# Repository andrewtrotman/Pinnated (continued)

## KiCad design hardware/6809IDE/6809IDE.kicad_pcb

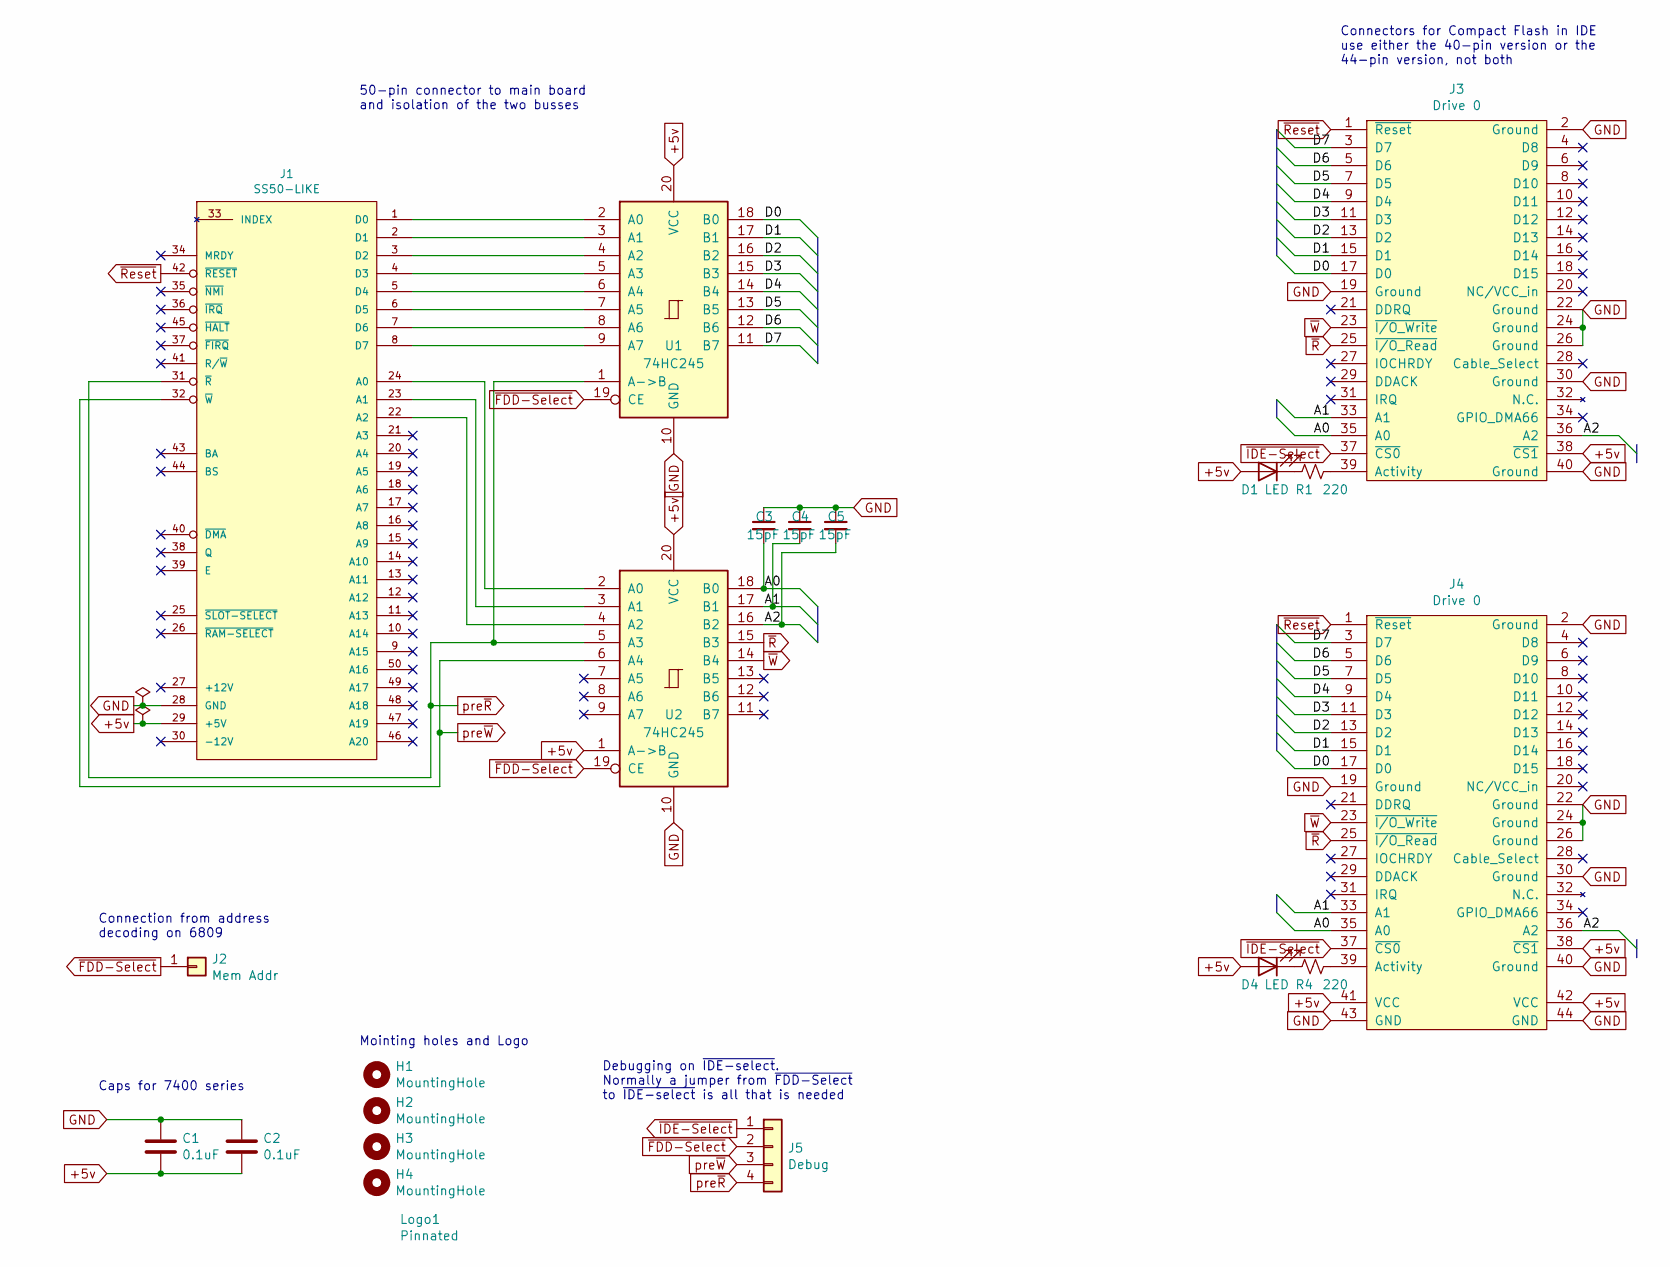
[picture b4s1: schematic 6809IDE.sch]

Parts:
C1, C2: 0.1uF; C_Disc_D5.0mm_W2.5mm_P5.00mm
C3, C4, C5: 15pF; C_Disc_D5.0mm_W2.5mm_P2.50mm
D1, D4: LED; LED_D5.0mm
H1, H2, H3, H4: MountingHole; MountingHole_3.2mm_M3_ISO14580_Pad
J1: SS50-LIKE; PinHeader_2x25_P2.54mm_Vertical
J2: Mem Addr; PinHeader_1x01_P2.54mm_Vertical
J3: Drive 0; PinHeader_2x20_P2.54mm_Vertical
J4: Drive 0; PinHeader_2x22_P2.00mm_Vertical
J5: Debug; PinHeader_1x04_P2.54mm_Vertical
Logo1: Pinnated; Pinnule
R1, R4: 220; R_Axial_DIN0309_L9.0mm_D3.2mm_P12.70mm_Horizontal
U1, U2: 74HC245; DIP-20_W7.62mm_LongPads

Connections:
+5v: C1.2, C2.2, D1.2 (A), D4.2 (A), J1.29 (+5V), J3.38 (~CS1), J4.38 (~CS1), J4.41 (VCC), J4.42 (VCC), U1.20 (VCC), U2.1 (A->B), U2.20 (VCC)
/A0: C3.2, J3.35 (A0), J4.35 (A0), U2.18 (B0)
/A1: C4.2, J3.33 (A1), J4.33 (A1), U2.17 (B1)
/A2: C5.2, J3.36 (A2), J4.36 (A2), U2.16 (B2)
/D0: J3.17 (D0), J4.17 (D0), U1.18 (B0)
/D1: J3.15 (D1), J4.15 (D1), U1.17 (B1)
/D2: J3.13 (D2), J4.13 (D2), U1.16 (B2)
/D3: J3.11 (D3), J4.11 (D3), U1.15 (B3)
/D4: J3.9 (D4), J4.9 (D4), U1.14 (B4)
/D5: J3.7 (D5), J4.7 (D5), U1.13 (B5)
/D6: J3.5 (D6), J4.5 (D6), U1.12 (B6)
/D7: J3.3 (D7), J4.3 (D7), U1.11 (B7)
GND: C1.1, C2.1, C3.1, C4.1, C5.1, J1.28 (GND), J3.2 (Ground), J3.19 (Ground), J3.22 (Ground), J3.24 (Ground), J3.26 (Ground), J3.30 (Ground), J3.40 (Ground), J4.2 (Ground), J4.19 (Ground), J4.22 (Ground), J4.24 (Ground), J4.26 (Ground), J4.30 (Ground), J4.40 (Ground), J4.43 (GND), J4.44 (GND), U1.10 (GND), U2.10 (GND)
unnamed: D1.1 (K), R1.2
unnamed: D4.1 (K), R4.2
unnamed: J1.1 (D0), U1.2 (A0)
unnamed: J1.2 (D1), U1.3 (A1)
unnamed: J1.3 (D2), U1.4 (A2)
unnamed: J1.4 (D3), U1.5 (A3)
unnamed: J1.5 (D4), U1.6 (A4)
unnamed: J1.6 (D5), U1.7 (A5)
unnamed: J1.7 (D6), U1.8 (A6)
unnamed: J1.8 (D7), U1.9 (A7)
unnamed: J1.22 (A2), U2.4 (A2)
unnamed: J1.23 (A1), U2.3 (A1)
unnamed: J1.24 (A0), U2.2 (A0)
unnamed: J3.39 (Activity), R1.1
unnamed: J4.39 (Activity), R4.1
pre~R: J1.31 (~R), J5.4, U1.1 (A->B), U2.5 (A3)
pre~W: J1.32 (~W), J5.3, U2.6 (A4)
~FDD-Select: J2.1, J5.2, U1.19 (CE), U2.19 (CE)
~IDE-Select: J3.37 (~CS0), J4.37 (~CS0), J5.1
~R: J3.25 (~I/O_Read), J4.25 (~I/O_Read), U2.15 (B3)
~Reset: J1.42 (~RESET), J3.1 (~Reset), J4.1 (~Reset)
~W: J3.23 (~I/O_Write), J4.23 (~I/O_Write), U2.14 (B4)

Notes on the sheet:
Debugging on ~IDE-select~. Normally a jumper from ~FDD-Select~ to ~IDE-select~ is all that is needed
Mointing holes and Logo
Caps for 7400 series
Connectors for Compact Flash in IDE use either the 40-pin version or the 44-pin version, not both
Connection from address decoding on 6809
50-pin connector to main board and isolation of the two busses

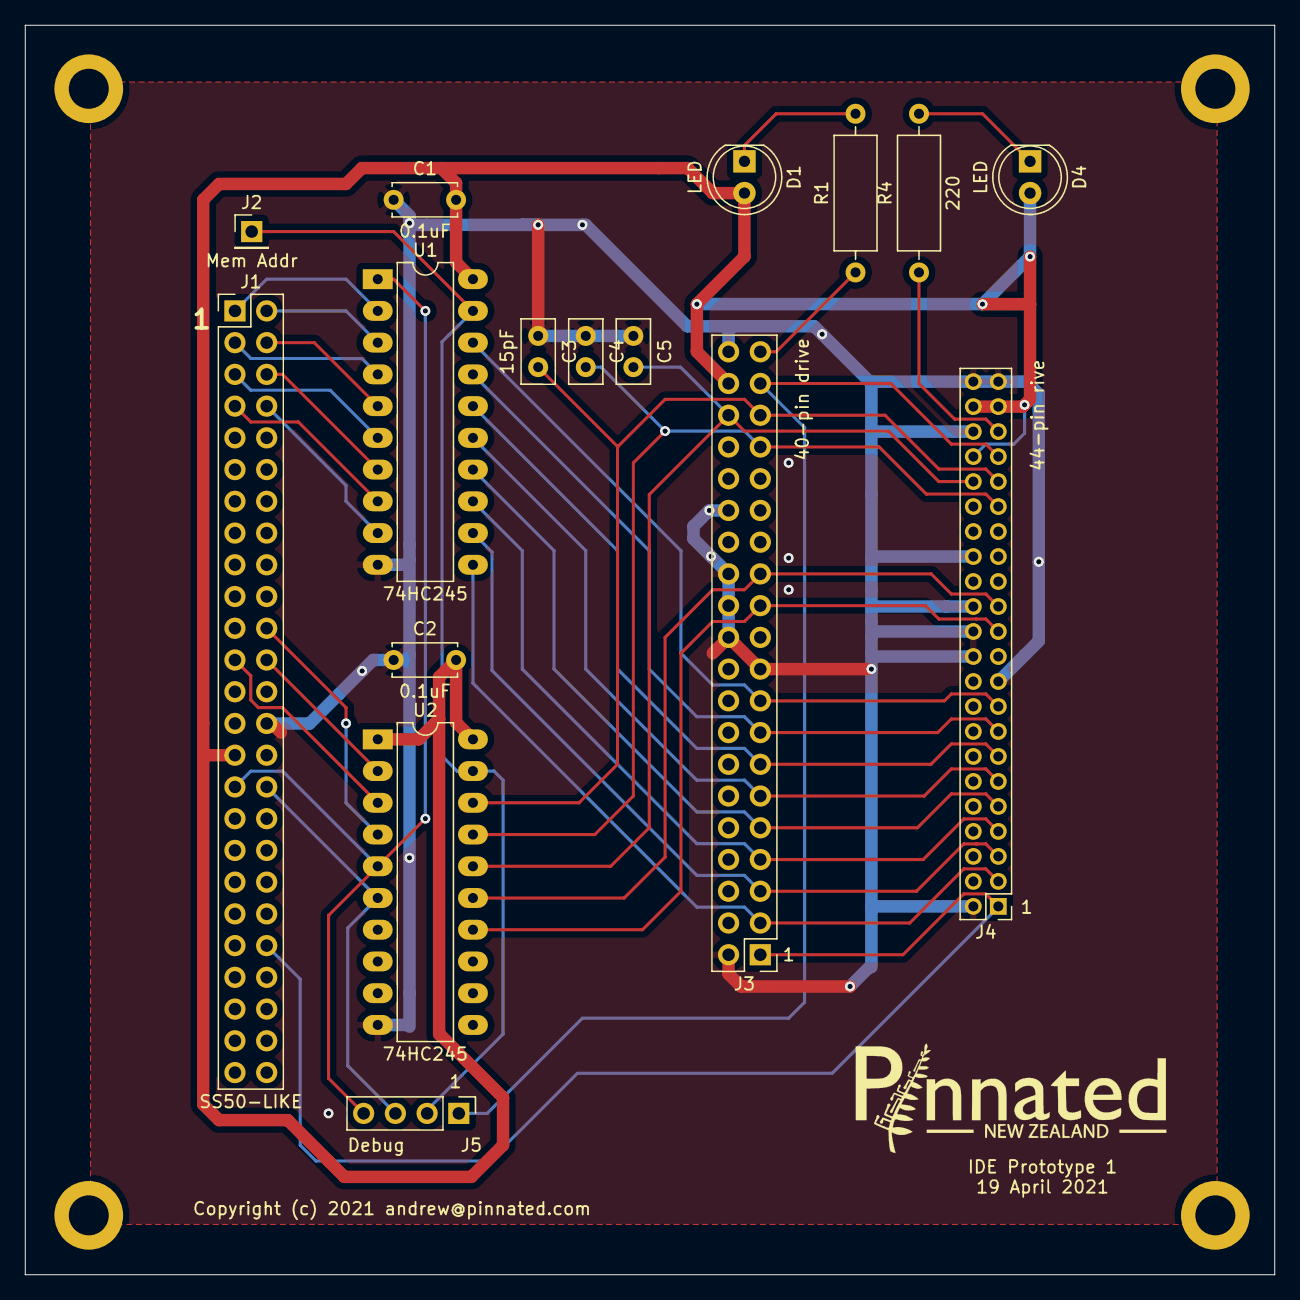
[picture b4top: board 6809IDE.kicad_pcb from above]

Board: 2 copper layers, 100.0 x 100.0 mm, 20 parts (0 on the bottom side), 35 nets.

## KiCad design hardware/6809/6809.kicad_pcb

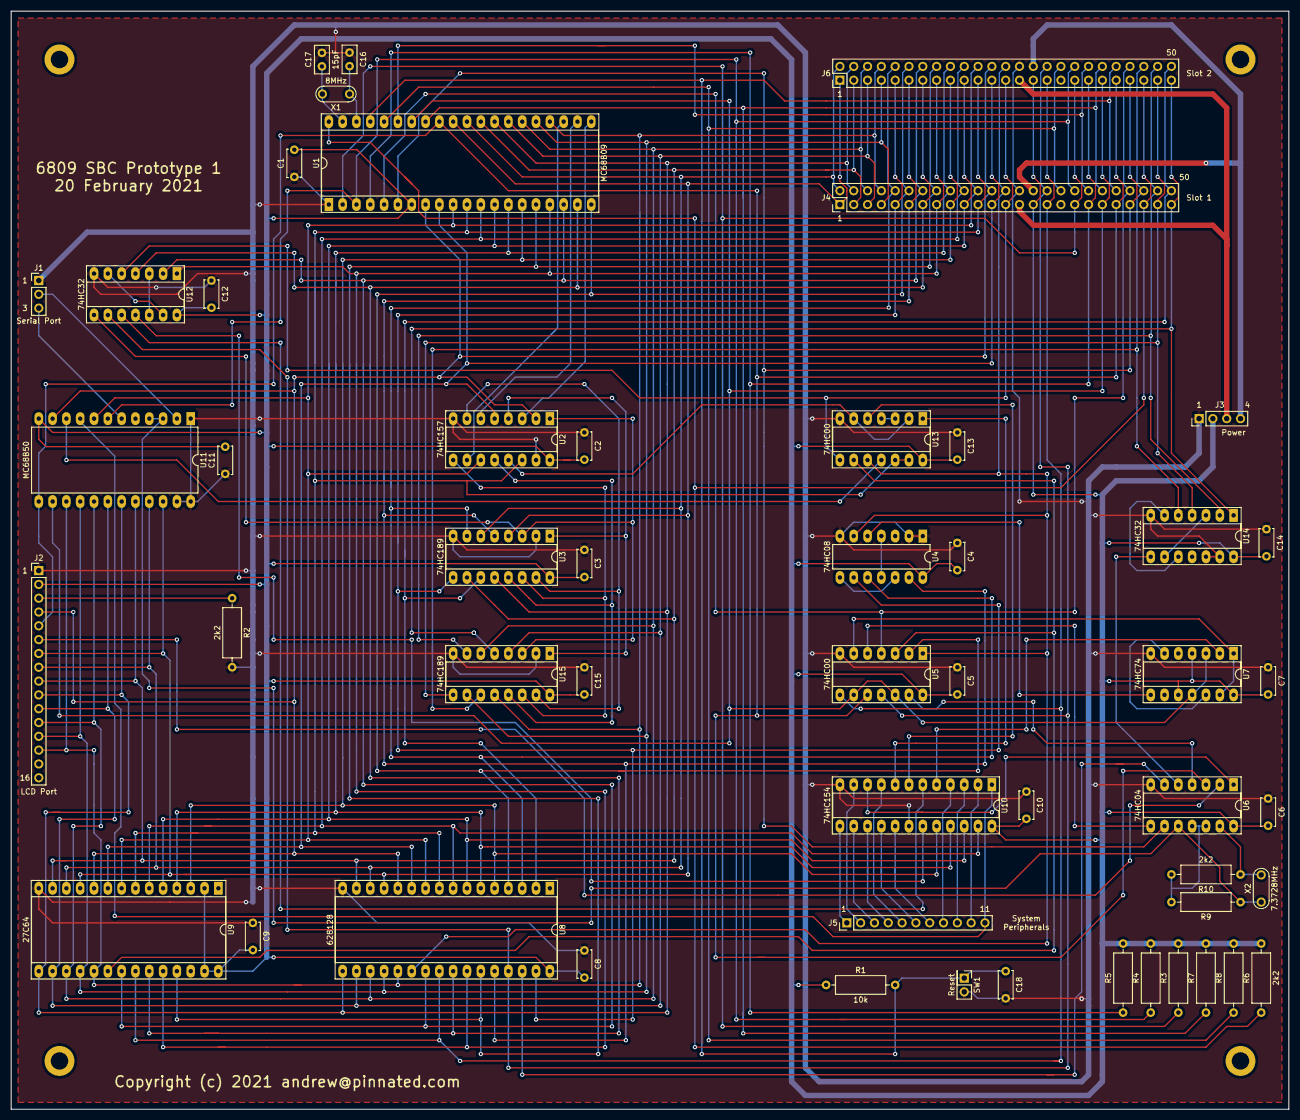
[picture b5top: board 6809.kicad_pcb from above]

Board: 2 copper layers, 235.0 x 201.9 mm, 56 parts (0 on the bottom side), 100 nets.

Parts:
C1, C2, C3, C4, C5, C6, C7, C8, C9, C10, C11, C12, C13, C14, C15, C18: 0.1uF; C_Disc_D5.0mm_W2.5mm_P5.00mm
C16, C17: 15pF; C_Disc_D5.0mm_W2.5mm_P2.50mm
H1, H2, H3, H4: MountingHole; MountingHole_3.2mm_M3_ISO14580_Pad
J1: Serial Port; PinHeader_1x03_P2.54mm_Vertical
J2: AMPIRE 162B LCD; PinHeader_1x16_P2.54mm_Vertical
J3: Power Connector; PinHeader_1x04_P2.54mm_Vertical
J4, J6: SS50-LIKE; PinHeader_2x25_P2.54mm_Vertical
J5: Conn_01x11; PinHeader_1x11_P2.54mm_Vertical
R1: 10k; R_Axial_DIN0309_L9.0mm_D3.2mm_P12.70mm_Horizontal
R2, R3, R4, R5, R6, R7, R8, R9, R10: 2k2; R_Axial_DIN0309_L9.0mm_D3.2mm_P12.70mm_Horizontal
SW1: Reset; PinHeader_2x01_P2.54mm_Vertical
U1: MC68B09; DIP-40_W15.24mm_Socket_LongPads
U2: 74HC157; DIP-16_W7.62mm_Socket_LongPads
U3, U15: 74HC189; DIP-16_W7.62mm_Socket_LongPads
U4: 74HC08; DIP-14_W7.62mm_LongPads
U5, U13: 74HC00; DIP-14_W7.62mm_Socket_LongPads
U6: 74HC04; DIP-14_W7.62mm_Socket_LongPads
U7: 74HC74; DIP-14_W7.62mm_Socket_LongPads
U8: 628128; DIP-32_W15.24mm_Socket_LongPads
U9: 27C64; DIP-28_W15.24mm_Socket_LongPads
U10: 74HC154; DIP-24_W7.62mm_Socket_LongPads
U11: MC68B50; DIP-24_W15.24mm_LongPads
U12, U14: 74HC32; DIP-14_W7.62mm_Socket_LongPads
X1: 8MHz; Resonator-2Pin_W7.0mm_H2.5mm
X2: 7.3728MHz; Resonator-2Pin_W7.0mm_H2.5mm

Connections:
+5v: C1.2, C2.2, C3.2, C4.2, C5.2, C6.2, C7.2, C8.2, C9.2, C10.2, C11.2, C12.2, C13.2, C14.2, C15.2, J2.2, J3.2, J4.29, J6.29, R1.1, R3.2, R4.2, R5.2, R6.2, R7.2, R8.2, U1.7, U2.16, U3.16, U4.14, U5.14, U6.14, U7.4, U7.10, U7.14, U8.32, U9.2, U9.27, U9.28, U10.24, U11.12, U12.14, U13.14, U14.14, U15.16
+12v: J3.3, J4.27, J6.27
-12v: J3.4, J4.30, J6.30
/A0: J2.4, J4.24, J6.24, U1.8, U2.2, U8.12, U9.10, U11.11
/A1: J4.23, J6.23, U1.9, U2.5, U8.11, U9.9
/A2: J4.22, J6.22, U1.10, U2.11, U8.10, U9.8, U11.8
/A3: J4.21, J6.21, U1.11, U2.14, U8.9, U9.7, U13.12, U13.13
/A4: J4.20, J6.20, U1.12, U8.8, U9.6, U10.23
/A5: J4.19, J6.19, U1.13, U8.7, U9.5, U10.22
/A6: J4.18, J6.18, U1.14, U8.6, U9.4, U10.21
/A7: J4.17, J6.17, U1.15, U8.5, U9.3, U10.20
/A8: J4.16, J6.16, U1.16, U8.27, U9.25
/A9: J4.15, J6.15, U1.17, U8.26, U9.24, U12.1
/A10: J4.14, J6.14, U1.18, U8.23, U9.21, U12.2
/A11: J4.13, J6.13, U1.19, U8.25, U9.23, U12.4
/A12: J4.12, J6.12, U1.20, U5.2, U8.4
/A13: J4.11, J6.11, U3.5, U4.13, U8.28
/A14: J4.10, J6.10, U3.7, U4.10, U8.3
/A15: J4.9, J6.9, U3.9, U4.9, U8.31
/A16: J4.50, J6.50, U3.11, U8.2
/A17: J4.49, J6.49, U14.1, U15.5
/A18: J4.48, J6.48, U14.2, U15.7
/A19: J4.47, J6.47, U14.4, U15.9
/A20: J4.46, J6.46, U14.5, U15.11
/AA13: U1.21, U2.3
/AA14: U1.22, U2.6
/AA15: U1.23, U2.10
/D0: J2.7, J4.1, J6.1, U1.31, U3.4, U8.13, U9.11, U11.22
/D1: J2.8, J4.2, J6.2, U1.30, U3.6, U8.14, U9.12, U11.21
/D2: J2.9, J4.3, J6.3, U1.29, U3.10, U8.15, U9.13, U11.20
/D3: J2.10, J4.4, J6.4, U1.28, U3.12, U8.17, U9.15, U11.19
/D4: J2.11, J4.5, J6.5, U1.27, U8.18, U9.16, U11.18, U15.4
/D5: J2.12, J4.6, J6.6, U1.26, U8.19, U9.17, U11.17, U15.6
/D6: J2.13, J4.7, J6.7, U1.25, U8.20, U9.18, U11.16, U15.10
/D7: J2.14, J4.8, J6.8, U1.24, U8.21, U9.19, U11.15, U15.12
BA: J4.43, J6.43, U1.6, U6.9
BS: J4.44, J6.44, U1.5, U5.4
DEVA-SELECT: J5.2, U10.11
DEVB-SELECT: J5.1, U10.13
DEVC-SELECT: J5.3, U10.14
DEVD-SELECT: J5.4, U10.15
DEVE-SELECT: J5.6, U10.16
DEVF-SELECT: J5.7, U10.17
E: J4.39, J6.39, U1.34, U5.9, U5.12, U7.3, U7.11, U11.14
GND: C1.1, C2.1, C3.1, C4.1, C5.1, C6.1, C7.1, C8.1, C9.1, C10.1, C11.1, C12.1, C13.1, C14.1, C15.1, C16.1, C17.2, C18.2, J1.1, J2.1, J3.1, J4.28, J6.28, R2.2, SW1.2, U1.1, U2.8, U2.15, U3.2, U3.8, U4.1, U4.2, U4.7, U5.7, U6.7, U7.7, U8.16, U9.14, U10.12, U10.18, U11.1, U11.23, U11.24, U12.7, U13.7, U14.7, U14.12, U14.13, U15.2, U15.8
MRDY: J4.34, J6.34, R8.1, U1.36
unnamed: C16.2, U1.38, X1.1
unnamed: C17.1, U1.39, X1.2
unnamed: J1.2, U11.2
unnamed: J1.3, U11.6
unnamed: J2.3, R2.1
unnamed: J2.6, U6.2
unnamed: R9.1, U6.10, U11.3, U11.4, X2.1
unnamed: R10.1, U6.13, X2.2
unnamed: R9.2, R10.2, U6.11, U6.12
unnamed: U4.4, U4.11
unnamed: U4.8, U4.12
unnamed: U5.5, U6.8
unnamed: U5.6, U7.1, U7.13
unnamed: U5.13, U6.4
unnamed: U6.6, U8.30
unnamed: U7.6, U7.12
unnamed: U10.19, U12.11
unnamed: U11.10, U13.11
unnamed: U2.1, U3.3, U12.8, U15.3
unnamed: U12.3, U12.12
unnamed: U12.6, U12.13
unnamed: U2.13, U13.2, U13.6
unnamed: U13.3, U13.4
unnamed: U14.3, U14.9
unnamed: U6.5, U14.8
unnamed: U14.6, U14.10
unnamed: U2.4, U3.1, U15.1
unnamed: U2.12, U3.13, U15.13
unnamed: U2.9, U3.14, U15.14
unnamed: U2.7, U3.15, U15.15
PROT: U4.5, U7.8
Q: J4.38, J6.38, U1.35
R|~W: J2.5, J4.41, J6.41, U1.32, U5.10, U6.3, U11.13
~DAT-SELECT: U10.6, U12.10
~DMA: J4.40, J6.40, R7.1, U1.33
~FDD-SELECT: J5.10, U10.2
~FIRQ: J4.37, J6.37, R5.1, U1.4
~FPU-SELECT: J5.5, U10.9
~HALT: J4.45, J6.45, R6.1, U1.40
~IRQ: J4.36, J6.36, R4.1, U1.3, U11.7
~LCD-SELECT: U6.1, U10.10
~LEAVE-PROT: U7.2, U10.5
~MAP1-SELECT: U10.7, U13.5
~MAP2-SELECT: U10.8, U13.1
~NET-SELECT: J5.8, U10.4
~NMI: J4.35, J6.35, R3.1, U1.2
~RAM-SELECT: J4.26, J6.26, U4.6, U5.1, U8.22, U13.10
~READ-ENABLE: J4.31, J6.31, U5.8, U8.24, U9.22
~RESET: C18.1, J4.42, J6.42, R1.2, SW1.1, U1.37
~ROM-SELECT: U5.3, U9.20, U13.9
~SERIAL-SELECT: J5.11, U10.1, U11.9
~SLOT-SELECT: J4.25, J6.25, U12.5, U13.8
~TIMER-SELECT: J5.9, U10.3
~WRITE-ENABLE: J4.32, J6.32, U5.11, U8.29, U12.9

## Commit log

2021-03-20 tools to test peripherals
2021-03-20 working on RAM DAC
2021-03-20 check ram works
2021-03-21 RAM and LCD test
2021-03-21 RAM and LCD test into modules
2021-03-21 check the DAT
2021-03-21 checks two different page tables
2021-03-21 serial methods
2021-03-21 white space
2021-03-27 FLEX compatible serial routines
2021-03-27 start work on the BIOS
2021-03-28 working starts of a BIOS
2021-03-28 correct for correct ORG address
2021-03-30 Boots into TinyBasic
2021-04-02 schematic and pcb
2021-04-02 text desplay
2021-04-02 KiCad files
2021-04-02 TinyBASIC
2021-04-03 ide comtroller
2021-04-05 display errors
2021-04-05 more modular
2021-04-05 added latches
2021-04-06 clean up
2021-04-09 IDE controller
2021-04-09 extras
2021-04-10 first attempt at FLEX methods
2021-04-10 qload
2021-04-11 FLEX loader
2021-04-11 FLEX loader from FLEX Adaptation Guide
2021-04-11 first write to a disk
2021-04-12 can load sectors from .dsk format disks
2021-04-13 boot FLEX on load
2021-04-16 boots FLEX
2021-04-16 move to 1 FLEX sector per IDE sector
2021-04-17 read and write to compactflash
2021-04-18 move to single connector
2021-04-24 start of ROM and RAM board
2021-04-24 schematic for ROM/RAM card
2021-04-25 ROMRAM board
2021-04-25 ground layers
2021-05-01 boots flex on IDE board
2021-05-03 added debugging
2021-05-06 prints diagnostics
2021-05-07 text card
2021-05-09 working on missing drives
2021-05-09 reads and writes
2021-05-09 fixed drive method
2021-05-09 working with diagnosticx
2021-05-09 fewer diagnostics
2021-05-09 remove diagnostis from read
2021-05-09 read without diagnostics
2021-05-09 write works with dead space
2021-05-09 write works with less dead space
2021-05-09 read and write both work
2021-05-14 clock and more
2021-05-15 digital logic wired up
2021-05-20 has a placement overlap
2021-05-22 expansion board
2021-05-23 finished and Gerbers generated
2021-06-14 how to generate C from ROMs
